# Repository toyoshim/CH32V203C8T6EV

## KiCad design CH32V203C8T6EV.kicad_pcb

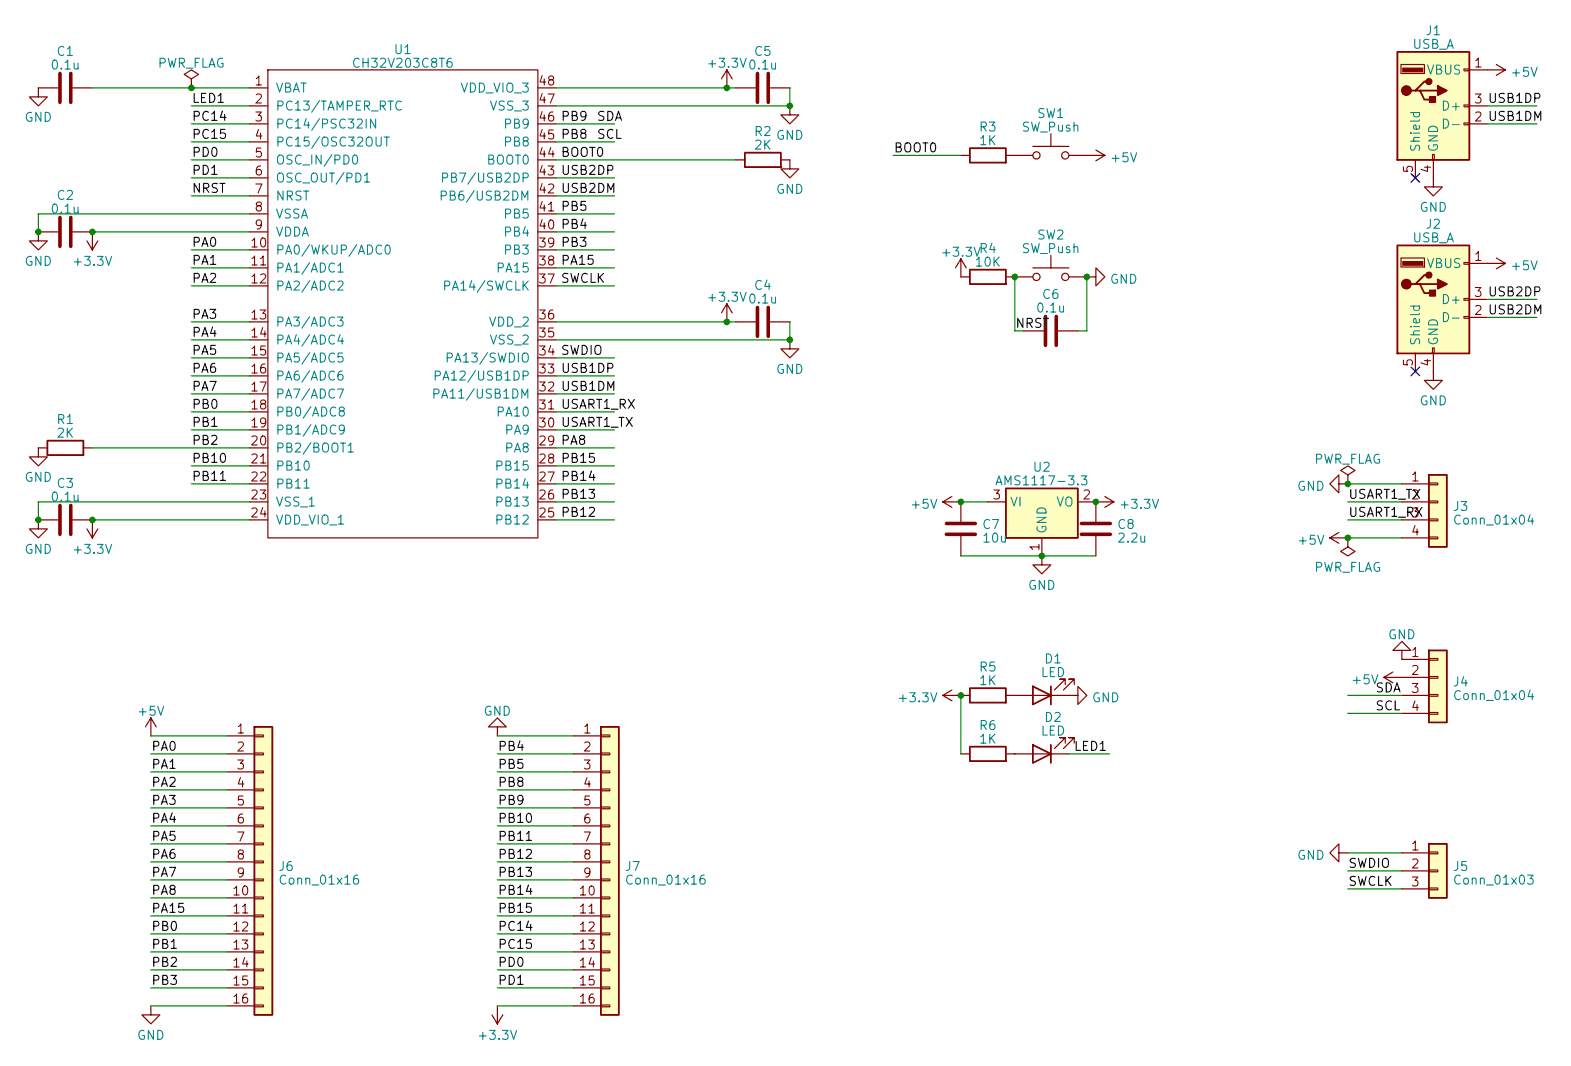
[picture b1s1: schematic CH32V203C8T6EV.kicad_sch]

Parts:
C1, C2, C3, C4, C5, C6: 0.1u; C_0402_1005Metric
C7: 10u; C_0402_1005Metric
C8: 2.2u; C_0402_1005Metric
D1, D2: LED; C_0603_1608Metric; LCSC C965807
J1, J2: USB_A; USB-A-TH_JTJ-USB-A-F-10.0-010; LCSC C42576
J3: Conn_01x04; PinHeader_1x04_P2.54mm_Vertical
J4: Conn_01x04; CONN-TH_4P-P2.00_HX20020-4A_2; LCSC C7429580
J5: Conn_01x03; PinHeader_1x03_P2.54mm_Vertical
J6, J7: Conn_01x16; PinHeader_1x16_P2.54mm_Vertical
R1, R2: 2K; R_0402_1005Metric
R3, R5, R6: 1K; R_0402_1005Metric
R4: 10K; R_0402_1005Metric
SW1, SW2: SW_Push; TS-1159B; LCSC C381055
U1: CH32V203C8T6; LQFP-48_7x7mm_P0.5mm; LCSC C3001172
U2: AMS1117-3.3; SOT-223-3_TabPin2; LCSC C347222

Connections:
+3.3V: C2.2, C3.2, C4.1, C5.1, C8.1, J7.16, R4.1, R5.1, R6.1, U1.9 (VDDA), U1.24 (VDD_VIO_1), U1.36 (VDD_2), U1.48 (VDD_VIO_3), U2.2 (VO)
+5V: C7.1, J1.1 (VBUS), J2.1 (VBUS), J3.4, J4.2, J6.1, SW1.2, U2.3 (VI)
/BOOT0: R2.1, R3.1, U1.44 (BOOT0)
/LED1: D2.1 (K), U1.2 (PC13/TAMPER_RTC)
/NRST: C6.1, R4.2, SW2.1, U1.7 (NRST)
/PA0: J6.2, U1.10 (PA0/WKUP/ADC0)
/PA1: J6.3, U1.11 (PA1/ADC1)
/PA2: J6.4, U1.12 (PA2/ADC2)
/PA3: J6.5, U1.13 (PA3/ADC3)
/PA4: J6.6, U1.14 (PA4/ADC4)
/PA5: J6.7, U1.15 (PA5/ADC5)
/PA6: J6.8, U1.16 (PA6/ADC6)
/PA7: J6.9, U1.17 (PA7/ADC7)
/PA8: J6.10, U1.29 (PA8)
/PA15: J6.11, U1.38 (PA15)
/PB0: J6.12, U1.18 (PB0/ADC8)
/PB1: J6.13, U1.19 (PB1/ADC9)
/PB2: J6.14, R1.2, U1.20 (PB2/BOOT1)
/PB3: J6.15, U1.39 (PB3)
/PB4: J7.2, U1.40 (PB4)
/PB5: J7.3, U1.41 (PB5)
/PB8: J4.4, J7.4, U1.45 (PB8)
/PB9: J4.3, J7.5, U1.46 (PB9)
/PB10: J7.6, U1.21 (PB10)
/PB11: J7.7, U1.22 (PB11)
/PB12: J7.8, U1.25 (PB12)
/PB13: J7.9, U1.26 (PB13)
/PB14: J7.10, U1.27 (PB14)
/PB15: J7.11, U1.28 (PB15)
/PC14: J7.12, U1.3 (PC14/PSC32IN)
/PC15: J7.13, U1.4 (PC15/OSC32OUT)
/PD0: J7.14, U1.5 (OSC_IN/PD0)
/PD1: J7.15, U1.6 (OSC_OUT/PD1)
/SWCLK: J5.3, U1.37 (PA14/SWCLK)
/SWDIO: J5.2, U1.34 (PA13/SWDIO)
/USART1_RX: J3.3, U1.31 (PA10)
/USART1_TX: J3.2, U1.30 (PA9)
/USB1DM: J1.2 (D-), U1.32 (PA11/USB1DM)
/USB1DP: J1.3 (D+), U1.33 (PA12/USB1DP)
/USB2DM: J2.2 (D-), U1.42 (PB6/USB2DM)
/USB2DP: J2.3 (D+), U1.43 (PB7/USB2DP)
GND: C1.1, C2.1, C3.1, C4.2, C5.2, C6.2, C7.2, C8.2, D1.1 (K), J1.4 (GND), J2.4 (GND), J3.1, J4.1, J5.1, J6.16, J7.1, R1.1, R2.2, SW2.2, U1.8 (VSSA), U1.23 (VSS_1), U1.35 (VSS_2), U1.47 (VSS_3), U2.1 (GND)
unnamed: C1.2, U1.1 (VBAT)
unnamed: D1.2 (A), R5.2
unnamed: D2.2 (A), R6.2
unnamed: R3.2, SW1.1

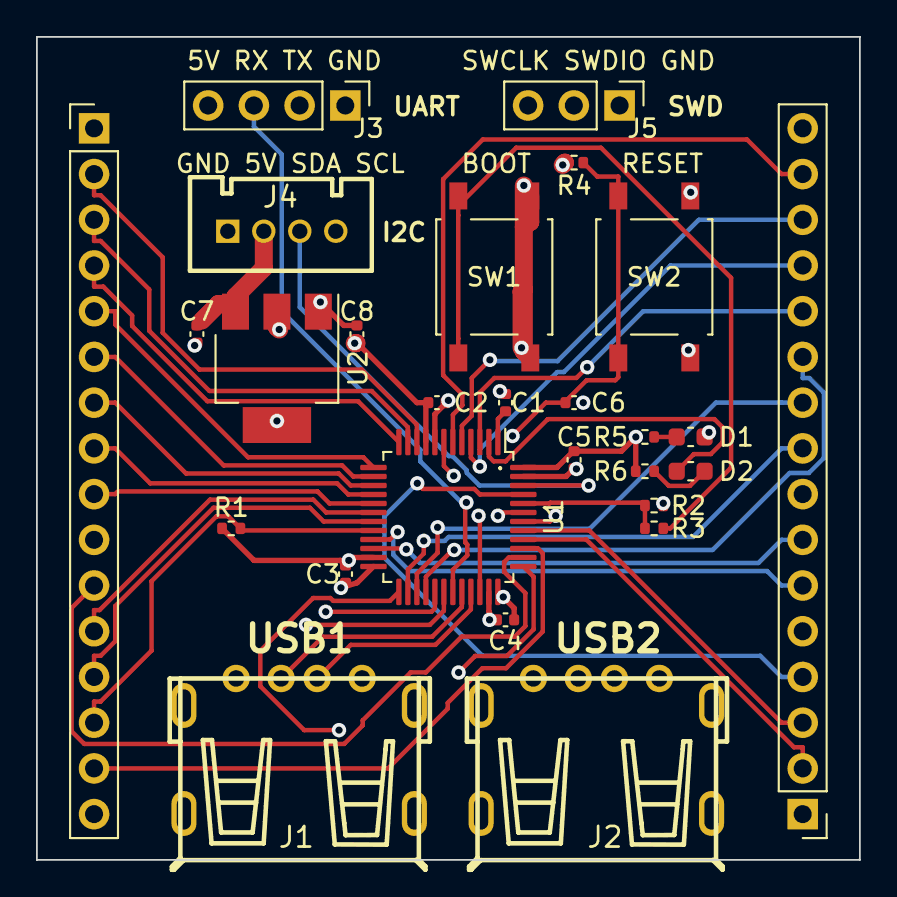
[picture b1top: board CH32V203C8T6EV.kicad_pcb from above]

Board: 4 copper layers, 45.7 x 45.7 mm, 27 parts (0 on the bottom side), 46 nets.

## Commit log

2023-12-28 initial
